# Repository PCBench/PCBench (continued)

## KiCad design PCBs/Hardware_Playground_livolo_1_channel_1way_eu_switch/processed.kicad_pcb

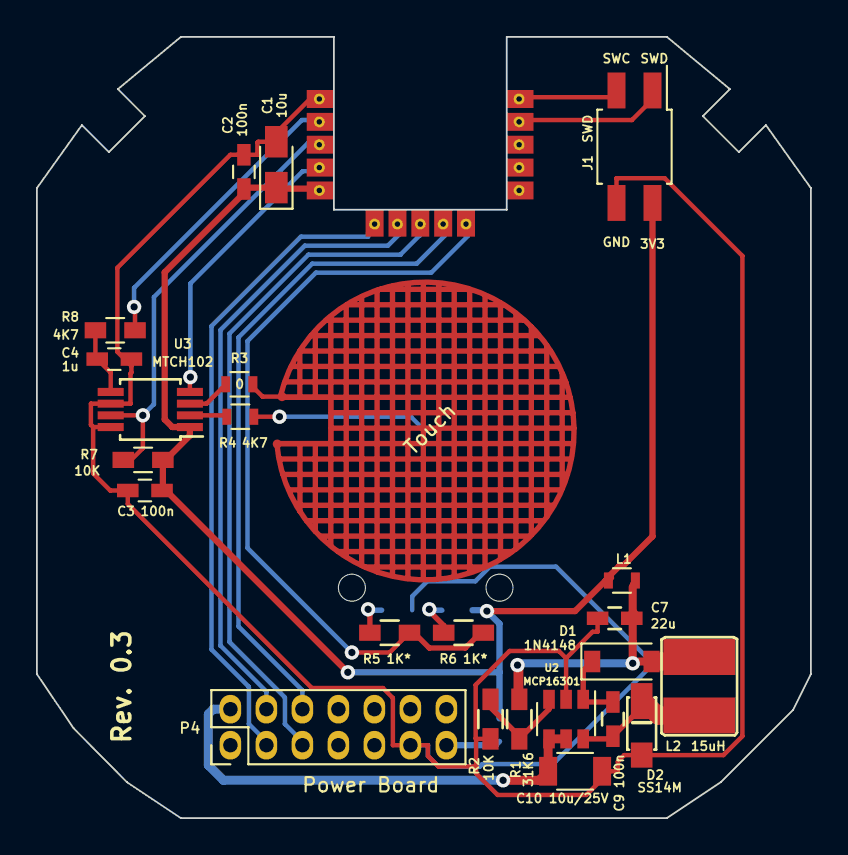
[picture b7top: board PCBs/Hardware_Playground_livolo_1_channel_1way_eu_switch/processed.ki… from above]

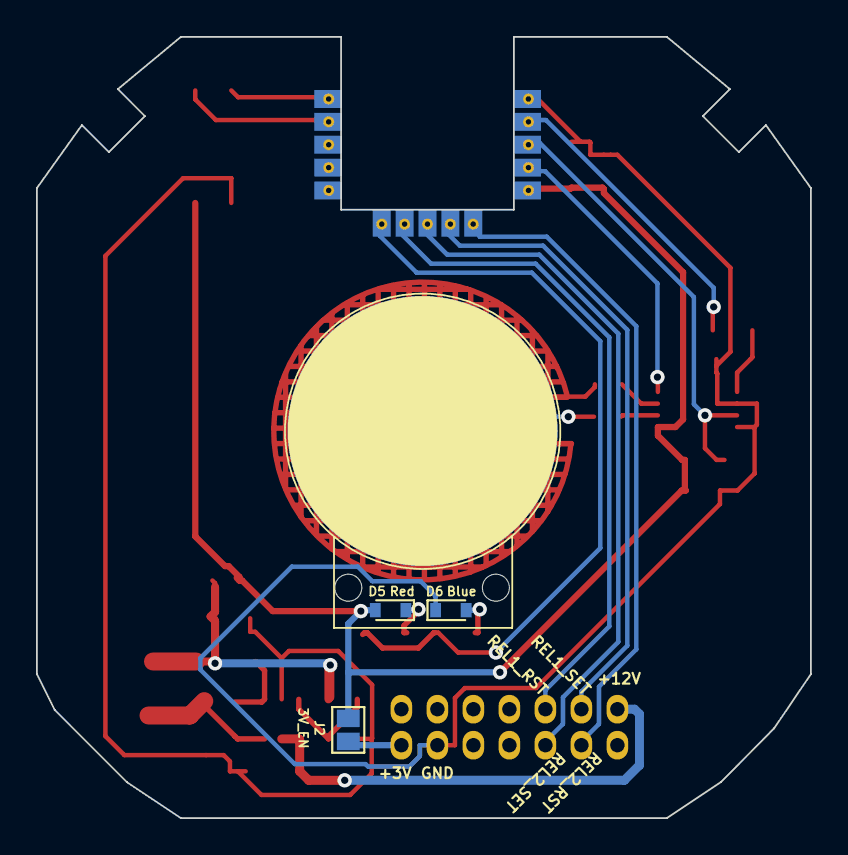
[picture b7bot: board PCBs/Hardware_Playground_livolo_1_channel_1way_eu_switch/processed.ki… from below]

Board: 2 copper layers, 43.0 x 43.4 mm, 28 parts (4 on the bottom side), 25 nets.

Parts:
C1: 10u; CP_Tantalum_Case-R_EIA-2012-12_Wave
C2, C3, C9: 100n; C_0603_HandSoldering
C4: 1u; C_0603_HandSoldering
C7: 22u; C_0603_HandSoldering
C10: 10u/25V; C_1206
D1: 1N4148; SOD-123
D2: SS14M
D5: Red; D_0603
D6: Blue; D_0603
J1: SWD; Pin_Header_Straight_2x02_Pitch2.00mm_SMD
J2: 3V_EN; GS2
L1: BLM18HE152SN1D; R_0603
L2: 15uH; VLCF4020T-150MR68
P4: Power Board; Pin_Header_Straight_2x07_Pitch2.00mm
R1: 31K6; R_0603_HandSoldering
R2, R7: 10K; R_0603_HandSoldering
R3: 0; R_0603
R4: 4K7; R_0603
R5, R6: 1K*; R_0603_HandSoldering
R8: 4K7; R_0603_HandSoldering
U1: Touch; livolo_ts_guard
U2: MCP16301; SOT-23-6
U3: MTCH102; MSOP-8_3x3mm_Pitch0.65mm
U5: H_NRF52832; Holyiot-NRF52832

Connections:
+3V3: C1.1, C2.2, C3.2, D5.2, J1.2, J2.1, L1.2, R7.2, U3.1, U5.5
/12Vcc: C10.1, P4.2, U2.4, U2.5
/MTPM: U3.4, U5.4
/MTSA: R8.1, U5.2
/Relay1_Reset: P4.6, U5.9
/Relay1_Set: P4.4, U5.7
/Relay2_Reset: P4.3, U5.6
/Relay2_Set: P4.5, U5.8
/S1_LEDs: R5.2, R6.2, U5.10
/SWCLK: J1.3, U5.15
/SWDIO: J1.1, U5.14
/TS1: R7.1, U3.7, U5.3
GND: C1.2, C2.1, C3.1, C4.2, C7.2, C10.2, D2.2, D6.1, J1.4, P4.11, R2.1, U2.2, U3.6, U3.8, U5.1
unnamed: C4.1, R8.2, U3.5
unnamed: C7.1, D1.2, L1.1, L2.1, R1.2
unnamed: C9.1, D1.1, U2.1
unnamed: C9.2, D2.1, L2.2, U2.6
unnamed: D5.1, R6.1
unnamed: D6.2, R5.1
unnamed: J2.2, P4.13
unnamed: R1.1, R2.2, U2.3
unnamed: R3.1, U3.3
unnamed: R3.2, U1.2
unnamed: R4.1, U3.2
unnamed: R4.2, U1.1
